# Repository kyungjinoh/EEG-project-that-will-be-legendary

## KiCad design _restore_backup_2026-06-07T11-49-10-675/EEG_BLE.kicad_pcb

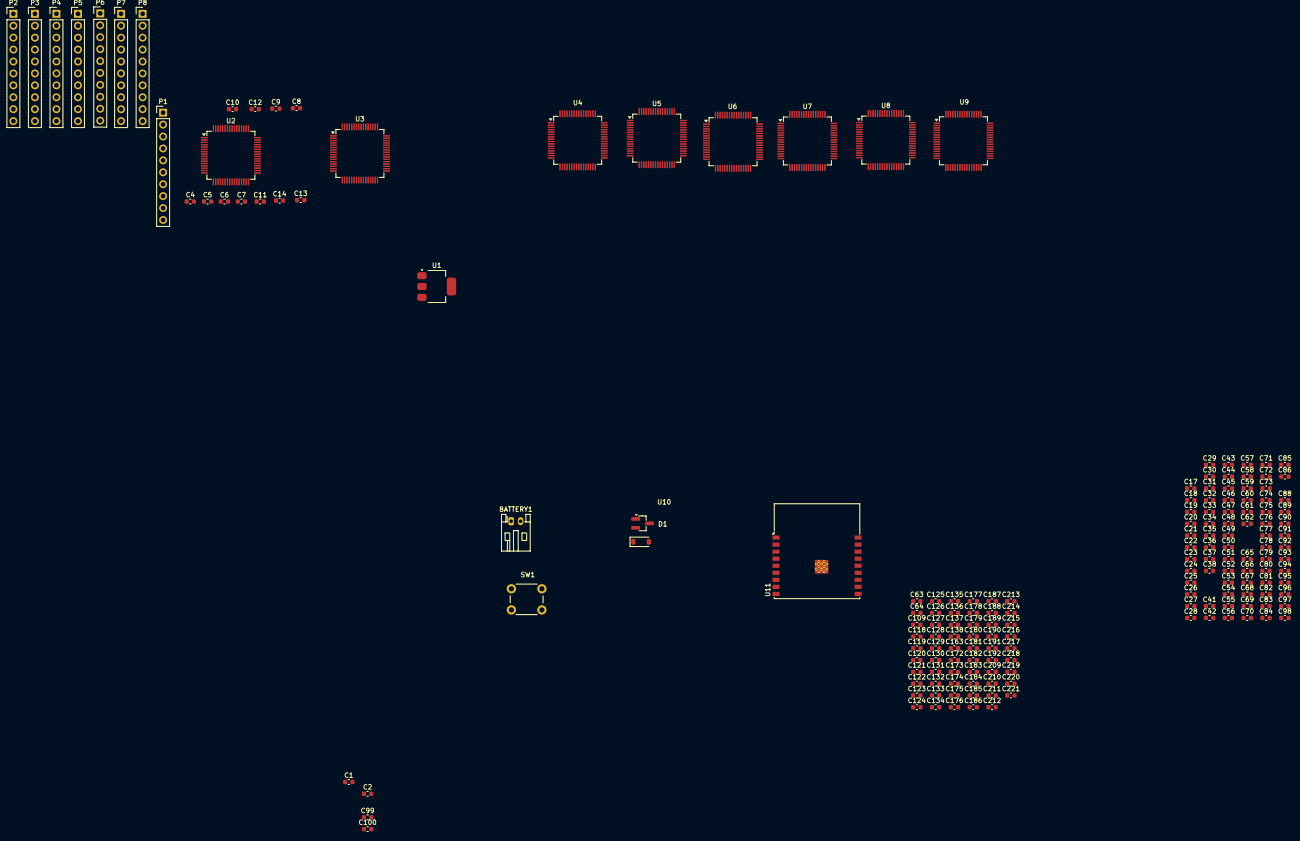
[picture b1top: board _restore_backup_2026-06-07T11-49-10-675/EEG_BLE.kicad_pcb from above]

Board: 4 copper layers, 173 parts (0 on the bottom side), 94 nets, no tracks yet.

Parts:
BATTERY1: 9V; JST_PH_S2B-PH-K_1x02_P2.00mm_Horizontal
C1: 0.33uF; C_0603_1608Metric
C2, C21, C23, C24, C28, C65, C66, C69, C70, C71, C73, C78, C81, C118, C121, C122, C124, C125, C128, C132, C135, C172, C175, C176, C178, C179, C182, C185, C190, C210, C212, C213, C217, C220, C221: 0.1uF; C_0603_1608Metric
C4, C5, C6, C7, C8, C9, C10, C11, C12, C13, C14, C17, C18, C31, C32, C33, C34, C35, C36, C37, C38, C41, C42, C43, C44, C45, C46, C47, C48, C49, C50, C51, C52, C53, C54, C55, C56, C57, C58, C59, C60, C61, C62, C85, C86, C88, C89, C90, C91, C92, C93, C94, C95, C96, C97, C98, C99, C100: 4n7; C_0603_1608Metric
C19, C63, C64, C109, C119, C163, C173, C209: 1uf; C_0603_1608Metric
C20: 1n; C_0603_1608Metric
C22, C26, C27, C30, C67, C68, C75, C76, C77, C79, C83, C84, C120, C123, C127, C130, C131, C134, C136, C138, C174, C177, C181, C184, C186, C188, C189, C192, C211, C215, C216, C219: 1uF; C_0603_1608Metric
C25, C72, C74, C126, C129, C180, C183, C214: 10uF; C_0603_1608Metric
C29, C80, C82, C133, C137, C187, C191, C218: 100uF; C_0603_1608Metric
D1: D; D_SOD-123
P1, P2, P3, P4, P5, P6, P7, P8: ELECTRODES; PinHeader_1x10_P2.54mm_Vertical
SW1: PUSH; SW_PUSH_6mm_H4.3mm
U1: LM1117MP-5.0; SOT-223-3_TabPin2
U2, U3, U4, U5, U6, U7, U8, U9: ADS1299; TQFP-64_10x10mm_P0.5mm
U10: AMS1117-3.3; SOT-23_Handsoldering
U11: ESP32-C3-WROOM-02

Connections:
/BIAS_DRV: C20.1, P1.1, P2.1, P3.1, P4.1, P5.1, P6.1, P7.1, P8.1
/BIAS_MASTER: C20.2, U2.62 (BIASIN), U2.63 (BIASOUT)
/CS: U2.39 (~CS), U3.39 (~CS), U4.39 (~CS), U5.39 (~CS), U6.39 (~CS), U7.39 (~CS), U8.39 (~CS), U9.39 (~CS), U11.7 (IO8)
/DAISY_U4: U3.41 (DAISY_IN), U4.43 (DOUT)
/DAISY_U5: U4.41 (DAISY_IN), U5.43 (DOUT)
/DAISY_U6: U5.41 (DAISY_IN), U6.43 (DOUT)
/DAISY_U7: U6.41 (DAISY_IN), U7.43 (DOUT)
/DAISY_U8: U7.41 (DAISY_IN), U8.43 (DOUT)
/DAISY_U9: U8.41 (DAISY_IN), U9.43 (DOUT)
/DRDY: U2.47 (~DRDY), U11.8 (IO9)
/EEG_REF: U2.18 (SRB2), U3.18 (SRB2), U4.18 (SRB2), U5.18 (SRB2), U6.18 (SRB2), U7.18 (SRB2), U8.18 (SRB2), U9.18 (SRB2)
/MASTER_CLK: U2.37 (CLK), U3.37 (CLK), U4.37 (CLK), U5.37 (CLK), U6.37 (CLK), U7.37 (CLK), U8.37 (CLK), U9.37 (CLK)
/REF_ELECTRODE: P1.2, P1.9, P2.2, P2.9, P3.2, P3.9, P4.2, P4.9, P5.2, P5.9, P6.2, P6.9, P7.2, P7.9, P8.2, P8.9, U2.1 (IN8N), U2.2 (IN8P), U2.3 (IN7N), U2.4 (IN7P), U2.5 (IN6N), U2.6 (IN6P), U2.7 (IN5N), U2.8 (IN5P), U2.9 (IN4N), U2.10 (IN4P), U2.11 (IN3N), U2.12 (IN3P), U2.13 (IN2N), U2.14 (IN2P), U2.15 (IN1N), U3.1 (IN8N), U3.2 (IN8P), U3.3 (IN7N), U3.4 (IN7P), U3.5 (IN6N), U3.6 (IN6P), U3.7 (IN5N), U3.8 (IN5P), U3.9 (IN4N), U3.10 (IN4P), U3.11 (IN3N), U3.12 (IN3P), U3.13 (IN2N), U3.14 (IN2P), U3.15 (IN1N), U4.1 (IN8N), U4.2 (IN8P), U4.3 (IN7N), U4.4 (IN7P), U4.5 (IN6N), U4.6 (IN6P), U4.7 (IN5N), U4.8 (IN5P), U4.9 (IN4N), U4.10 (IN4P), U4.11 (IN3N), U4.12 (IN3P), U4.13 (IN2N), U4.14 (IN2P), U4.15 (IN1N), U5.1 (IN8N), U5.2 (IN8P), U5.3 (IN7N), U5.4 (IN7P), U5.5 (IN6N), U5.6 (IN6P), U5.7 (IN5N), U5.8 (IN5P), U5.9 (IN4N), U5.10 (IN4P), U5.11 (IN3N), U5.12 (IN3P), U5.13 (IN2N), U5.14 (IN2P), U5.15 (IN1N), U6.1 (IN8N), U6.2 (IN8P), U6.3 (IN7N), U6.4 (IN7P), U6.5 (IN6N), U6.6 (IN6P), U6.7 (IN5N), U6.8 (IN5P), U6.9 (IN4N), U6.10 (IN4P), U6.11 (IN3N), U6.12 (IN3P), U6.13 (IN2N), U6.14 (IN2P), U6.15 (IN1N), U7.1 (IN8N), U7.2 (IN8P), U7.3 (IN7N), U7.4 (IN7P), U7.5 (IN6N), U7.6 (IN6P), U7.7 (IN5N), U7.8 (IN5P), U7.9 (IN4N), U7.10 (IN4P), U7.11 (IN3N), U7.12 (IN3P), U7.13 (IN2N), U7.14 (IN2P), U7.15 (IN1N), U8.1 (IN8N), U8.2 (IN8P), U8.3 (IN7N), U8.4 (IN7P), U8.5 (IN6N), U8.6 (IN6P), U8.7 (IN5N), U8.8 (IN5P), U8.9 (IN4N), U8.10 (IN4P), U8.11 (IN3N), U8.12 (IN3P), U8.13 (IN2N), U8.14 (IN2P), U8.15 (IN1N), U9.1 (IN8N), U9.2 (IN8P), U9.3 (IN7N), U9.4 (IN7P), U9.5 (IN6N), U9.6 (IN6P), U9.7 (IN5N), U9.8 (IN5P), U9.9 (IN4N), U9.10 (IN4P), U9.11 (IN3N), U9.12 (IN3P), U9.13 (IN2N), U9.14 (IN2P), U9.15 (IN1N)
/RESET: U2.36 (~RESET), U3.36 (~RESET), U4.36 (~RESET), U5.36 (~RESET), U6.36 (~RESET), U7.36 (~RESET), U8.36 (~RESET), U9.36 (~RESET), U11.3 (IO4)
/SCLK: U2.40 (SCLK), U3.40 (SCLK), U4.40 (SCLK), U5.40 (SCLK), U6.40 (SCLK), U7.40 (SCLK), U8.40 (SCLK), U9.40 (SCLK), U11.13 (IO18)
/SPI_MISO: U3.43 (DOUT), U11.4 (IO5)
/SPI_MOSI: U2.34 (DIN), U3.34 (DIN), U4.34 (DIN), U5.34 (DIN), U6.34 (DIN), U7.34 (DIN), U8.34 (DIN), U9.34 (DIN), U11.6 (IO7)
/START: U2.38 (START), U3.38 (START), U4.38 (START), U5.38 (START), U6.38 (START), U7.38 (START), U8.38 (START), U9.38 (START), U11.10 (IO10)
AGND: BATTERY1.2, C1.2, C2.1, C2.2, C220.2, C221.2, U1.1 (GND), U1.2 (VO), U2.31 (RESV1), U2.33 (DGND), U2.41 (DAISY_IN), U2.42 (GPIO1), U2.44 (GPIO2), U2.45 (GPIO3), U2.46 (GPIO4), U2.49 (DGND), U2.51 (DGND), U3.31 (RESV1), U3.33 (DGND), U3.42 (GPIO1), U3.44 (GPIO2), U3.45 (GPIO3), U3.46 (GPIO4), U3.49 (DGND), U3.51 (DGND), U3.52 (CLKSEL), U4.31 (RESV1), U4.33 (DGND), U4.42 (GPIO1), U4.44 (GPIO2), U4.45 (GPIO3), U4.46 (GPIO4), U4.49 (DGND), U4.51 (DGND), U4.52 (CLKSEL), U5.31 (RESV1), U5.33 (DGND), U5.42 (GPIO1), U5.44 (GPIO2), U5.45 (GPIO3), U5.46 (GPIO4), U5.49 (DGND), U5.51 (DGND), U5.52 (CLKSEL), U6.31 (RESV1), U6.33 (DGND), U6.42 (GPIO1), U6.44 (GPIO2), U6.45 (GPIO3), U6.46 (GPIO4), U6.49 (DGND), U6.51 (DGND), U6.52 (CLKSEL), U7.31 (RESV1), U7.33 (DGND), U7.42 (GPIO1), U7.44 (GPIO2), U7.45 (GPIO3), U7.46 (GPIO4), U7.49 (DGND), U7.51 (DGND), U7.52 (CLKSEL), U8.31 (RESV1), U8.33 (DGND), U8.42 (GPIO1), U8.44 (GPIO2), U8.45 (GPIO3), U8.46 (GPIO4), U8.49 (DGND), U8.51 (DGND), U8.52 (CLKSEL), U9.31 (RESV1), U9.33 (DGND), U9.41 (DAISY_IN), U9.42 (GPIO1), U9.44 (GPIO2), U9.45 (GPIO3), U9.46 (GPIO4), U9.49 (DGND), U9.51 (DGND), U9.52 (CLKSEL), U10.3 (GND), U11.9 (GND), U11.19 (GND)
AVDD: C19.1, C21.1, C22.1, C23.1, C63.1, C64.1, C65.1, C66.1, C67.1, C68.1, C69.1, C70.1, C109.1, C118.1, C119.1, C120.1, C121.1, C122.1, C123.1, C124.1, C163.1, C172.1, C173.1, C174.1, C175.1, C176.1, C177.1, C178.1, C209.1, C210.1, C211.1, C212.1, U2.19 (AVDD), U2.21 (AVDD), U2.22 (AVDD), U2.54 (AVDD1), U2.56 (AVDD), U2.59 (AVDD), U3.19 (AVDD), U3.21 (AVDD), U3.22 (AVDD), U3.54 (AVDD1), U3.56 (AVDD), U3.59 (AVDD), U4.19 (AVDD), U4.21 (AVDD), U4.22 (AVDD), U4.54 (AVDD1), U4.56 (AVDD), U4.59 (AVDD), U5.19 (AVDD), U5.21 (AVDD), U5.22 (AVDD), U5.54 (AVDD1), U5.56 (AVDD), U5.59 (AVDD), U6.19 (AVDD), U6.21 (AVDD), U6.22 (AVDD), U6.54 (AVDD1), U6.56 (AVDD), U6.59 (AVDD), U7.19 (AVDD), U7.21 (AVDD), U7.22 (AVDD), U7.54 (AVDD1), U7.56 (AVDD), U7.59 (AVDD), U8.19 (AVDD), U8.21 (AVDD), U8.22 (AVDD), U8.54 (AVDD1), U8.56 (AVDD), U8.59 (AVDD), U9.19 (AVDD), U9.21 (AVDD), U9.22 (AVDD), U9.54 (AVDD1), U9.56 (AVDD), U9.59 (AVDD)
AVSS: C4.1, C4.2, C8.1, C9.1, C10.1, C11.1, C12.1, C13.1, C14.1, C17.1, C18.1, C19.2, C21.2, C22.2, C23.2, C24.1, C24.2, C25.1, C25.2, C26.1, C27.2, C28.1, C29.2, C30.2, C31.1, C31.2, C32.1, C32.2, C36.1, C36.2, C37.1, C37.2, C38.1, C44.1, C45.1, C46.1, C47.1, C48.1, C49.1, C50.1, C51.1, C52.1, C53.1, C54.1, C55.1, C56.1, C57.1, C58.1, C59.1, C60.1, C61.1, C62.1, C63.2, C64.2, C65.2, C66.2, C67.2, C68.2, C69.2, C70.2, C71.1, C71.2, C72.1, C72.2, C73.1, C73.2, C74.1, C74.2, C75.1, C76.2, C77.1, C78.1, C79.2, C80.2, C81.1, C82.2, C83.2, C84.2, C85.1, C85.2, C86.1, C86.2, C90.1, C91.1, C91.2, C92.1, C92.2, C93.1, C94.1, C98.1, C99.1, C100.1, C109.2, C118.2, C119.2, C120.2, C121.2, C122.2, C123.2, C124.2, C125.1, C125.2, C126.1, C126.2, C127.1, C128.1, C128.2, C129.1, C129.2, C130.2, C131.1, C132.1, C133.2, C134.2, C135.1, C136.2, C137.2, C138.2, C163.2, C172.2, C173.2, C174.2, C175.2, C176.2, C177.2, C178.2, C179.1, C179.2, C180.1, C180.2, C181.1, C182.1, C182.2, C183.1, C183.2, C184.2, C185.1, C186.1, C187.2, C188.2, C189.2, C190.1, C191.2, C192.2, C209.2, C210.2, C211.2, C212.2, C213.1, C213.2, C214.1, C214.2, C215.1, C216.2, C217.1, C218.2, C219.2, U2.17 (SRB1), U2.20 (AVSS), U2.23 (AVSS), U2.24 (VREFP), U2.25 (VREFN), U2.32 (AVSS), U2.53 (AVSS1), U2.57 (AVSS), U2.58 (AVSS), U3.17 (SRB1), U3.20 (AVSS), U3.23 (AVSS), U3.24 (VREFP), U3.25 (VREFN), U3.32 (AVSS), U3.53 (AVSS1), U3.57 (AVSS), U3.58 (AVSS), U4.17 (SRB1), U4.20 (AVSS), U4.23 (AVSS), U4.24 (VREFP), U4.25 (VREFN), U4.32 (AVSS), U4.53 (AVSS1), U4.57 (AVSS), U4.58 (AVSS), U5.17 (SRB1), U5.20 (AVSS), U5.23 (AVSS), U5.24 (VREFP), U5.25 (VREFN), U5.32 (AVSS), U5.53 (AVSS1), U5.57 (AVSS), U5.58 (AVSS), U6.17 (SRB1), U6.20 (AVSS), U6.23 (AVSS), U6.24 (VREFP), U6.25 (VREFN), U6.32 (AVSS), U6.53 (AVSS1), U6.57 (AVSS), U6.58 (AVSS), U7.17 (SRB1), U7.20 (AVSS), U7.23 (AVSS), U7.24 (VREFP), U7.25 (VREFN), U7.32 (AVSS), U7.53 (AVSS1), U7.57 (AVSS), U7.58 (AVSS), U8.17 (SRB1), U8.20 (AVSS), U8.23 (AVSS), U8.24 (VREFP), U8.25 (VREFN), U8.32 (AVSS), U8.53 (AVSS1), U8.57 (AVSS), U8.58 (AVSS), U9.17 (SRB1), U9.20 (AVSS), U9.23 (AVSS), U9.24 (VREFP), U9.25 (VREFN), U9.32 (AVSS), U9.53 (AVSS1), U9.57 (AVSS), U9.58 (AVSS)
DVDD: C221.1, U2.35 (~PWDN), U2.48 (DVDD), U2.50 (DVDD), U2.52 (CLKSEL), U3.35 (~PWDN), U3.48 (DVDD), U3.50 (DVDD), U4.35 (~PWDN), U4.48 (DVDD), U4.50 (DVDD), U5.35 (~PWDN), U5.48 (DVDD), U5.50 (DVDD), U6.35 (~PWDN), U6.48 (DVDD), U6.50 (DVDD), U7.35 (~PWDN), U7.48 (DVDD), U7.50 (DVDD), U8.35 (~PWDN), U8.48 (DVDD), U8.50 (DVDD), U9.35 (~PWDN), U9.48 (DVDD), U9.50 (DVDD), U10.1 (VOUT), U11.1 (3V3), U11.2 (EN)
unnamed: BATTERY1.1, SW1.1
unnamed: D1.2 (A), SW1.2
unnamed: C6.1, C9.2, P1.3
unnamed: C7.1, C10.2, P1.4
unnamed: C5.1, C8.2, P1.5
unnamed: C6.2, P1.6
unnamed: C7.2, P1.7
unnamed: C5.2, P1.8
unnamed: P1.10, U2.16 (IN1P)
unnamed: C34.1, P2.3
unnamed: C35.1, P2.4
unnamed: C33.1, C38.2, P2.5
unnamed: C34.2, P2.6
unnamed: C35.2, P2.7
unnamed: C33.2, P2.8
unnamed: P2.10, U3.16 (IN1P)
unnamed: C42.1, C45.2, P3.3
unnamed: C43.1, C46.2, P3.4
unnamed: C41.1, C44.2, P3.5
unnamed: C42.2, P3.6
unnamed: C43.2, P3.7
unnamed: C41.2, P3.8
unnamed: P3.10, U4.16 (IN1P)
unnamed: C88.1, C93.2, P4.3
unnamed: C89.1, C94.2, P4.4
unnamed: C90.2, P4.5
unnamed: C88.2, P4.6
unnamed: C89.2, P4.7
unnamed: P4.10, U5.16 (IN1P)
unnamed: C96.1, C99.2, P5.3
unnamed: C97.1, C100.2, P5.4
unnamed: C95.1, C98.2, P5.5
unnamed: C96.2, P5.6
unnamed: C97.2, P5.7
unnamed: C95.2, P5.8
unnamed: P5.10, U6.16 (IN1P)
unnamed: P6.10, U7.16 (IN1P)
unnamed: P7.10, U8.16 (IN1P)
unnamed: P8.10, U9.16 (IN1P)
unnamed: C29.1, U2.28 (VCAP1)
unnamed: C30.1, U2.30 (VCAP2)
unnamed: C26.2, C28.2, U2.55 (VCAP3)
unnamed: C27.1, U2.26 (VCAP4)
unnamed: C80.1, U3.28 (VCAP1)
unnamed: C83.1, U3.30 (VCAP2)
unnamed: C75.2, C78.2, U3.55 (VCAP3)
unnamed: C76.1, U3.26 (VCAP4)
unnamed: C82.1, U4.28 (VCAP1)
unnamed: C84.1, U4.30 (VCAP2)
unnamed: C77.2, C81.2, U4.55 (VCAP3)
unnamed: C79.1, U4.26 (VCAP4)
unnamed: C133.1, U5.28 (VCAP1)
unnamed: C136.1, U5.30 (VCAP2)
unnamed: C127.2, C132.2, U5.55 (VCAP3)
unnamed: C130.1, U5.26 (VCAP4)
unnamed: C137.1, U6.28 (VCAP1)
unnamed: C138.1, U6.30 (VCAP2)
unnamed: C131.2, C135.2, U6.55 (VCAP3)
unnamed: C134.1, U6.26 (VCAP4)
unnamed: C187.1, U7.28 (VCAP1)
unnamed: C189.1, U7.30 (VCAP2)
unnamed: C181.2, C185.2, U7.55 (VCAP3)
unnamed: C184.1, U7.26 (VCAP4)
unnamed: C191.1, U8.28 (VCAP1)
unnamed: C192.1, U8.30 (VCAP2)
unnamed: C186.2, C190.2, U8.55 (VCAP3)
unnamed: C188.1, U8.26 (VCAP4)
unnamed: C218.1, U9.28 (VCAP1)
unnamed: C219.1, U9.30 (VCAP2)
unnamed: C215.2, C217.2, U9.55 (VCAP3)
unnamed: C216.1, U9.26 (VCAP4)
RAW: C1.1, C220.1, D1.1 (K), U1.3 (VI), U10.2 (VIN)

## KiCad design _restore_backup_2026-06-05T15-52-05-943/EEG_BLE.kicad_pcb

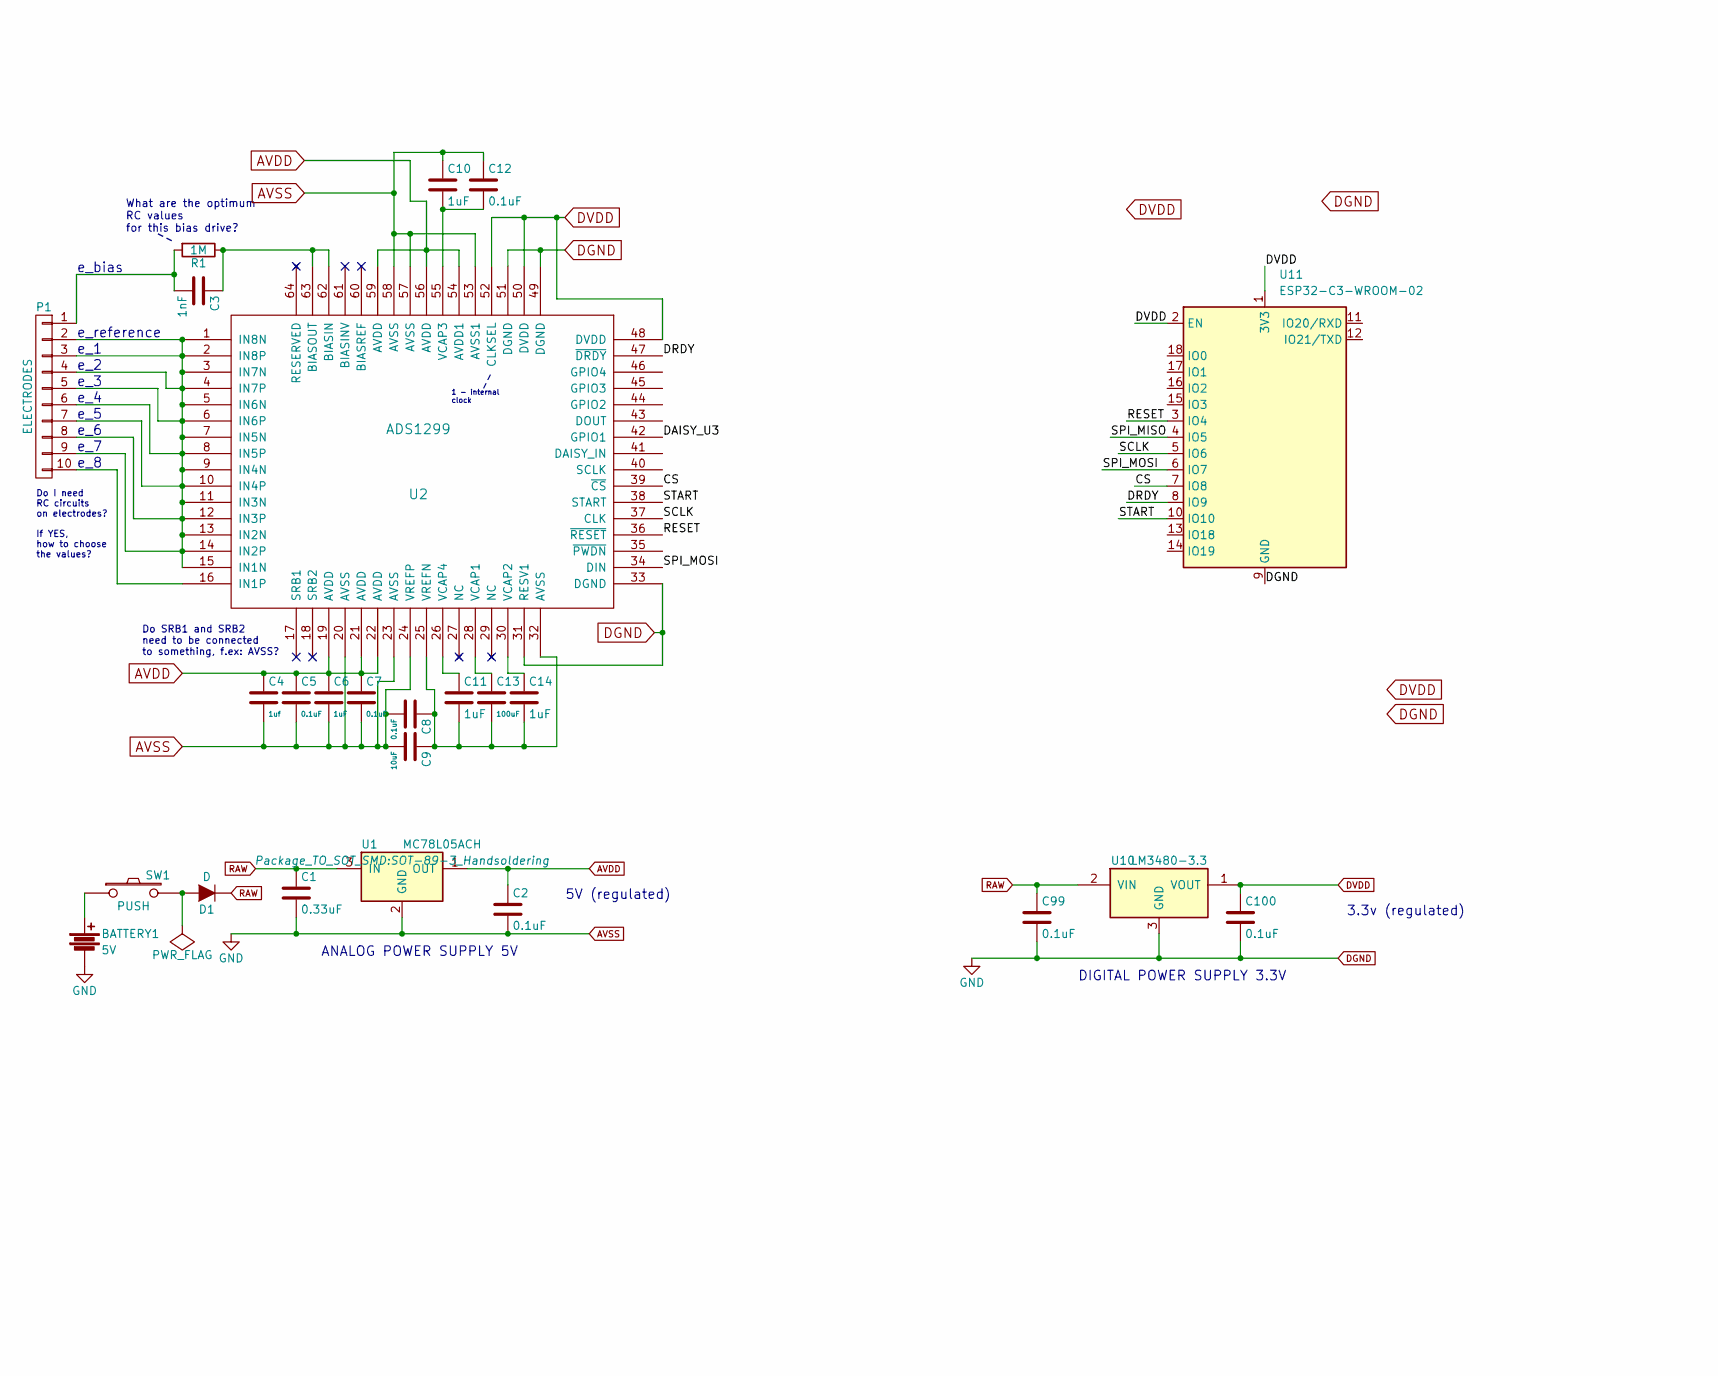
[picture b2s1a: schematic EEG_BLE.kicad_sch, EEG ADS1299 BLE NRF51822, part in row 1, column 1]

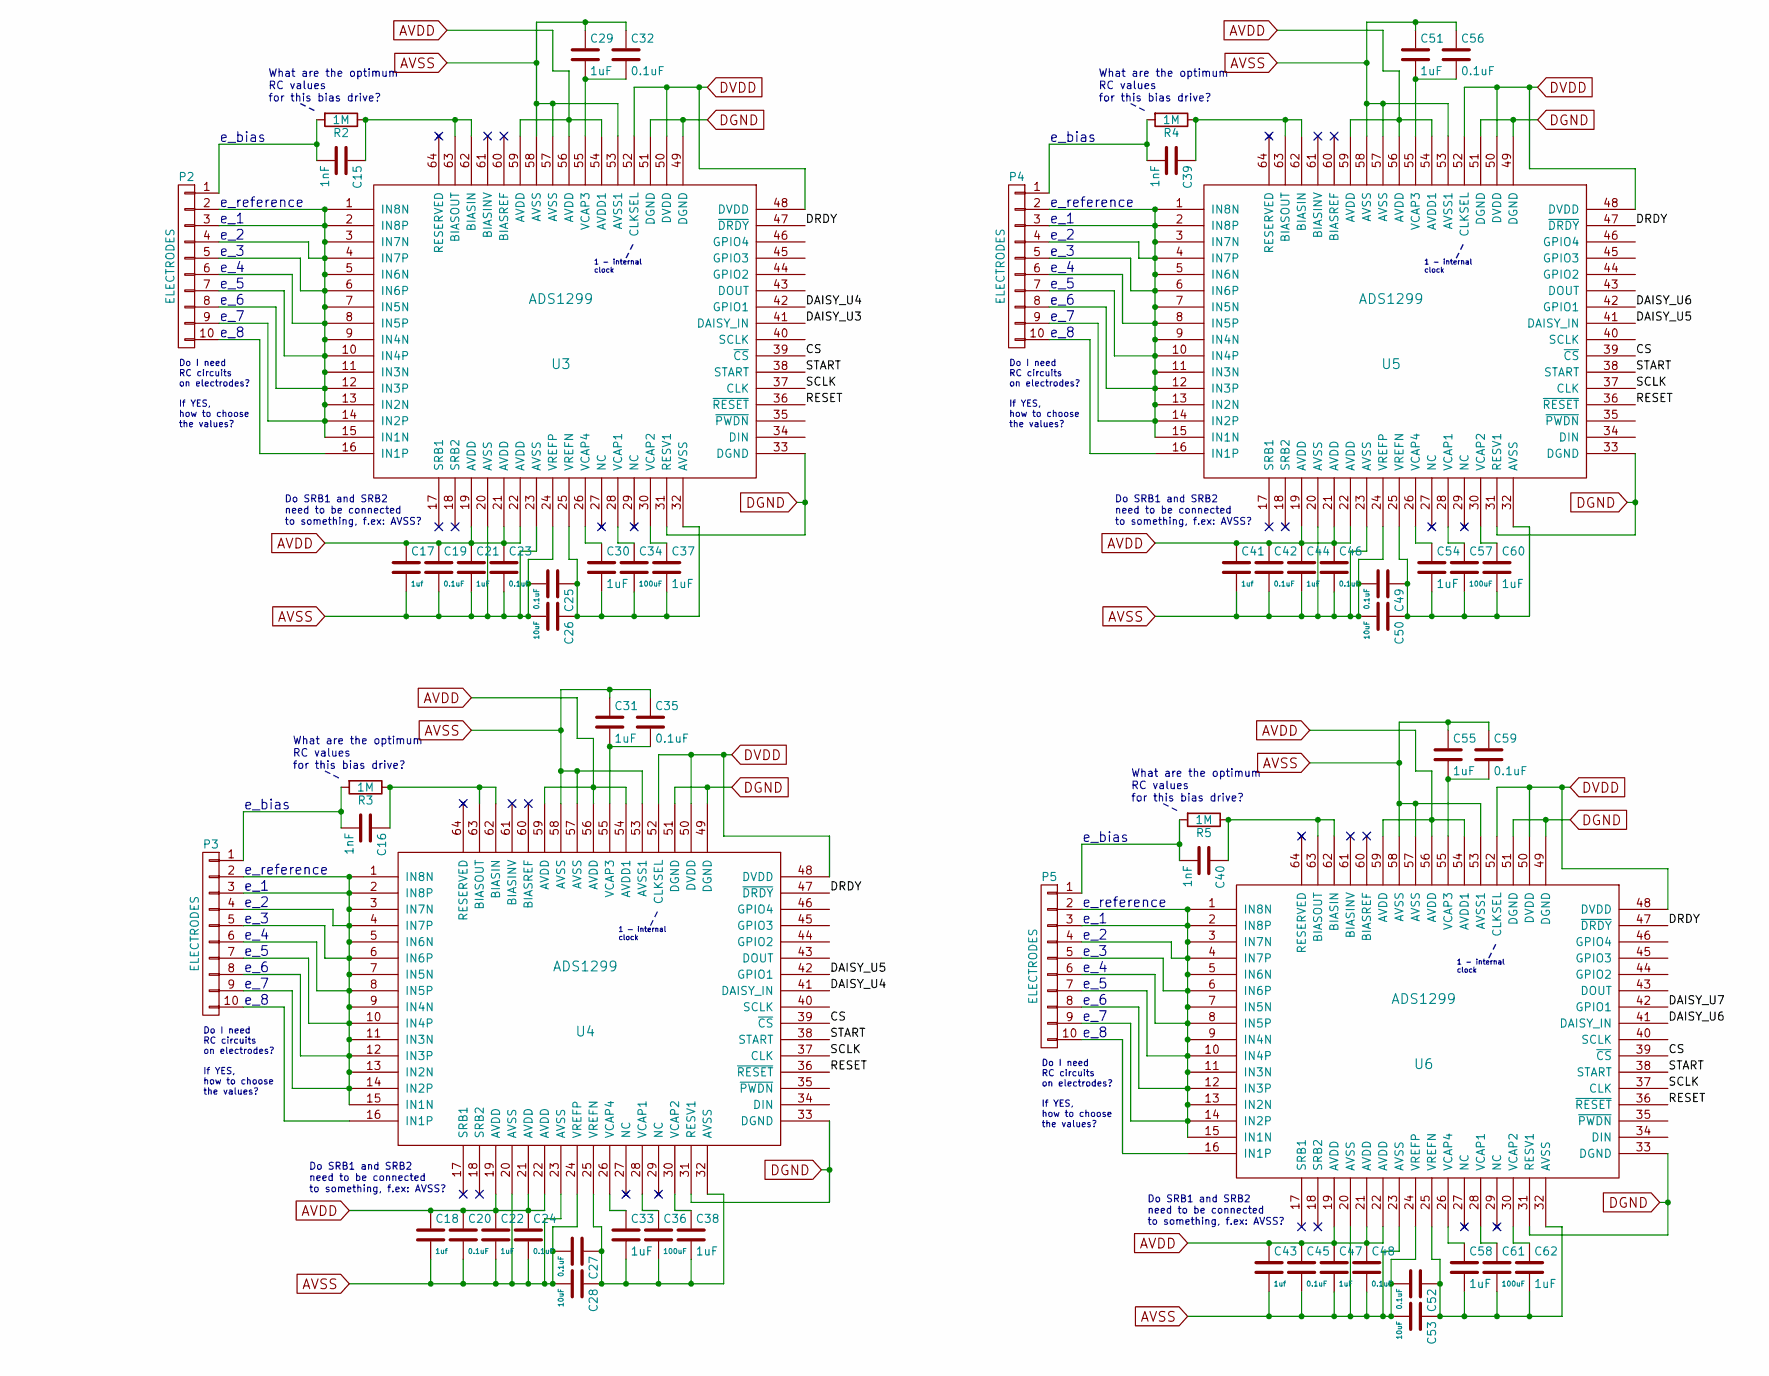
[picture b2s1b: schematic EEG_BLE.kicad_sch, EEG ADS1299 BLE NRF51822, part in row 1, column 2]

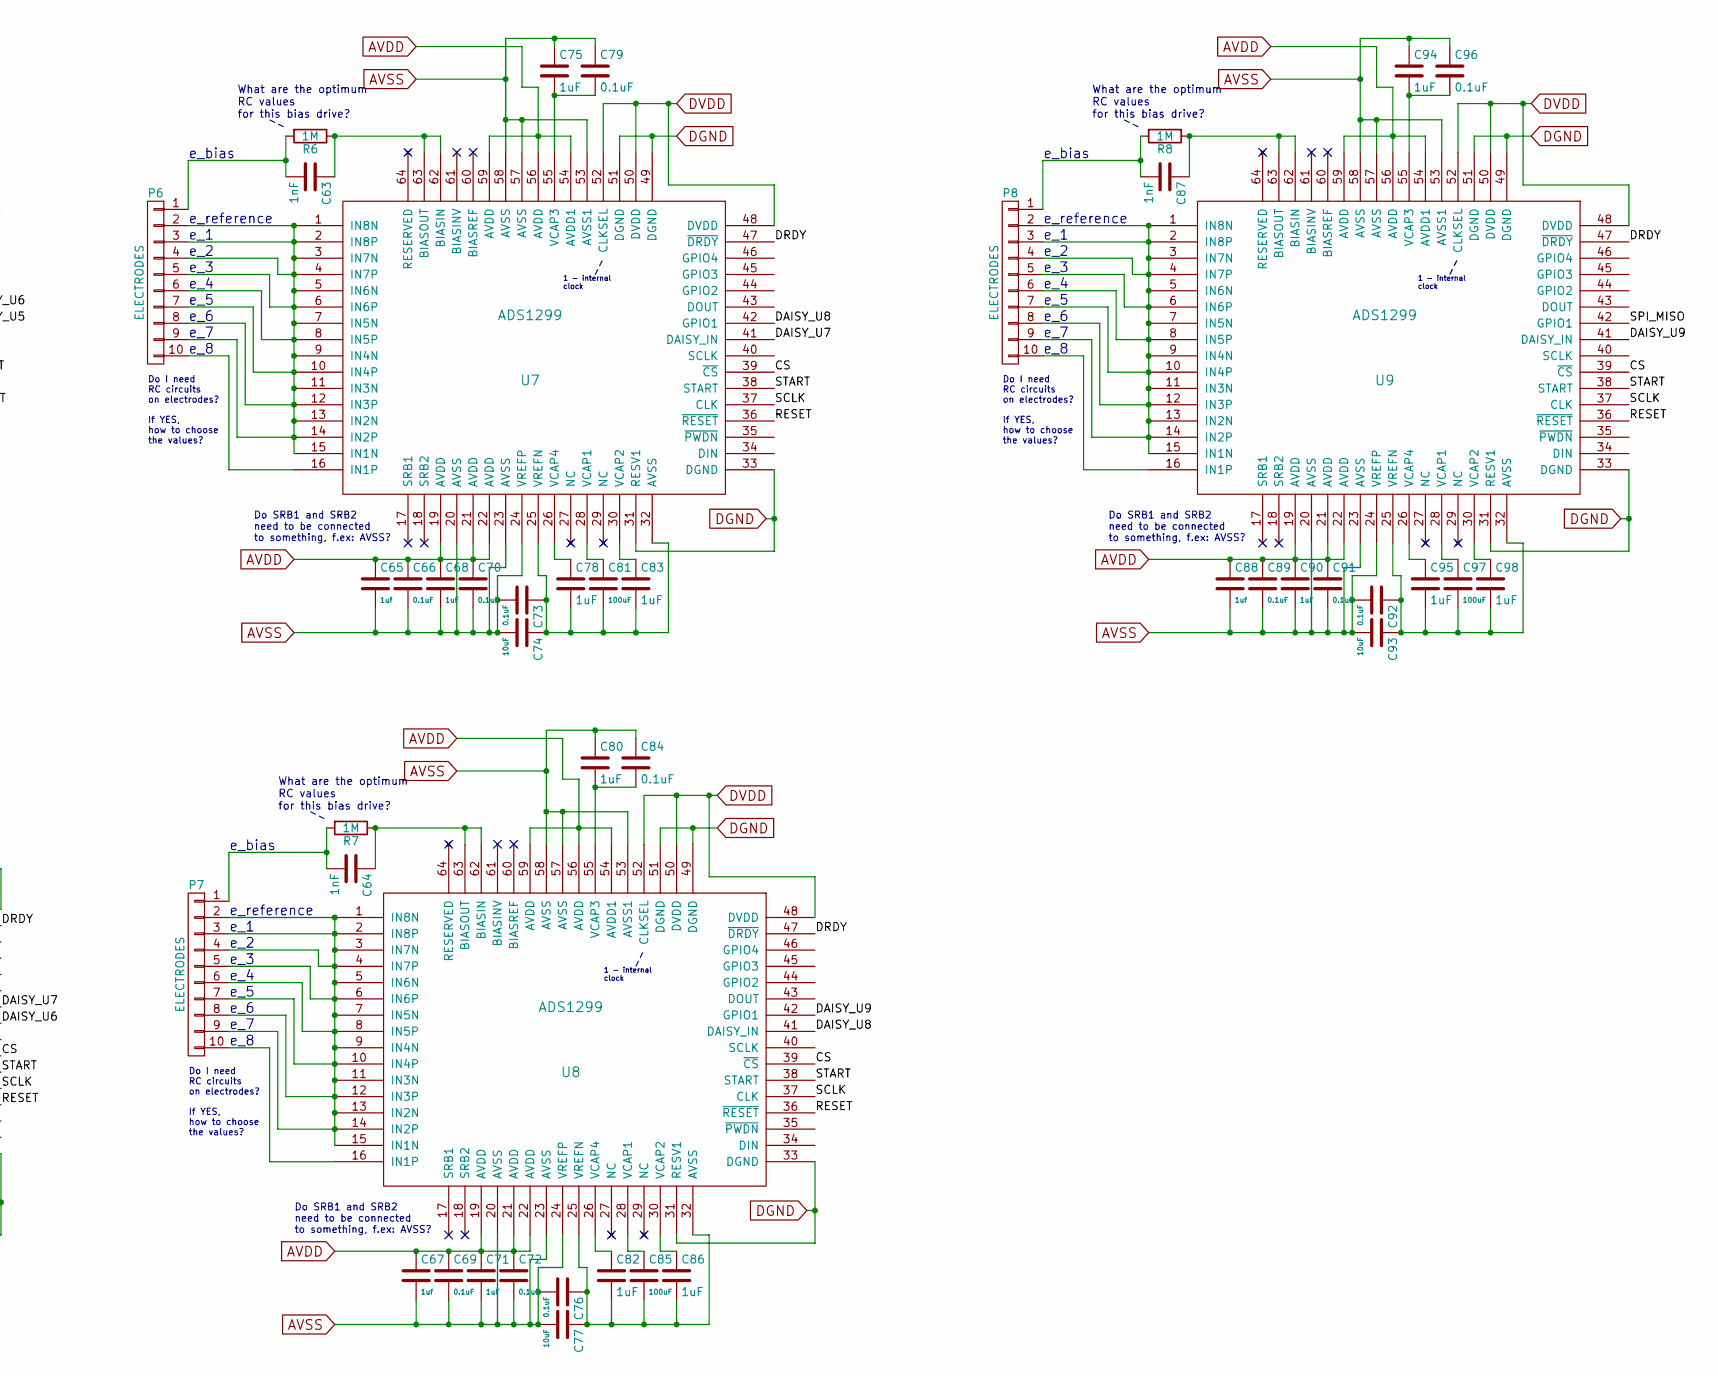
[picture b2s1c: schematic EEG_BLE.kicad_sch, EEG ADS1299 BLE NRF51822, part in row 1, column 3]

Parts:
BATTERY1: 5V; JST_PH_S2B-PH-K_1x02_P2.00mm_Horizontal
C1: 0.33uF; C_0603_1608Metric
C2, C5, C7, C8, C12, C19, C20, C23, C24, C25, C27, C32, C35, C42, C45, C46, C48, C49, C52, C56, C59, C66, C69, C70, C72, C73, C76, C79, C84, C89, C91, C92, C96, C99, C100: 0.1uF; C_0603_1608Metric
C3, C15, C16, C39, C40, C63, C64, C87: 1nF; C_0603_1608Metric
C4, C17, C18, C41, C43, C65, C67, C88: 1uf; C_0603_1608Metric
C6, C10, C11, C14, C21, C22, C29, C30, C31, C33, C37, C38, C44, C47, C51, C54, C55, C58, C60, C62, C68, C71, C75, C78, C80, C82, C83, C86, C90, C94, C95, C98: 1uF; C_0603_1608Metric
C9, C26, C28, C50, C53, C74, C77, C93: 10uF; C_0603_1608Metric
C13, C34, C36, C57, C61, C81, C85, C97: 100uF; C_0603_1608Metric
D1: D; D_SOD-123
P1, P2, P3, P4, P5, P6, P7, P8: ELECTRODES; PinHeader_1x10_P2.54mm_Vertical
R1, R2, R3, R4, R5, R6, R7, R8: 1M; R_0603_1608Metric
SW1: PUSH; SW_PUSH_6mm_H4.3mm
U1: MC78L05ACH; SOT-89-3_Handsoldering
U2, U3, U4, U5, U6, U7, U8, U9: ADS1299; TQFP-64_10x10mm_P0.5mm
U10: LM3480-3.3; SOT-23_Handsoldering
U11: ESP32-C3-WROOM-02

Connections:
/CS: U2.39 (~CS), U3.39 (~CS), U4.39 (~CS), U5.39 (~CS), U6.39 (~CS), U7.39 (~CS), U8.39 (~CS), U9.39 (~CS), U11.7 (IO8)
/DAISY_U3: U2.42 (GPIO1), U3.41 (DAISY_IN)
/DAISY_U4: U3.42 (GPIO1), U4.41 (DAISY_IN)
/DAISY_U5: U4.42 (GPIO1), U5.41 (DAISY_IN)
/DAISY_U6: U5.42 (GPIO1), U6.41 (DAISY_IN)
/DAISY_U7: U6.42 (GPIO1), U7.41 (DAISY_IN)
/DAISY_U8: U7.42 (GPIO1), U8.41 (DAISY_IN)
/DAISY_U9: U8.42 (GPIO1), U9.41 (DAISY_IN)
/DRDY: U2.47 (~DRDY), U3.47 (~DRDY), U4.47 (~DRDY), U5.47 (~DRDY), U6.47 (~DRDY), U7.47 (~DRDY), U8.47 (~DRDY), U9.47 (~DRDY), U11.8 (IO9)
/RESET: U2.36 (~RESET), U3.36 (~RESET), U4.36 (~RESET), U5.36 (~RESET), U6.36 (~RESET), U7.36 (~RESET), U8.36 (~RESET), U9.36 (~RESET), U11.3 (IO4)
/SCLK: U2.37 (CLK), U3.37 (CLK), U4.37 (CLK), U5.37 (CLK), U6.37 (CLK), U7.37 (CLK), U8.37 (CLK), U9.37 (CLK), U11.5 (IO6)
/SPI_MISO: U9.42 (GPIO1), U11.4 (IO5)
/SPI_MOSI: U2.34 (DIN), U11.6 (IO7)
/START: U2.38 (START), U3.38 (START), U4.38 (START), U5.38 (START), U6.38 (START), U7.38 (START), U8.38 (START), U9.38 (START), U11.10 (IO10)
AVDD: C2.1, C4.1, C5.1, C6.1, C7.1, C17.1, C18.1, C19.1, C20.1, C21.1, C22.1, C23.1, C24.1, C41.1, C42.1, C43.1, C44.1, C45.1, C46.1, C47.1, C48.1, C65.1, C66.1, C67.1, C68.1, C69.1, C70.1, C71.1, C72.1, C88.1, C89.1, C90.1, C91.1, U1.1 (OUT), U2.19 (AVDD), U2.21 (AVDD), U2.22 (AVDD), U2.54 (AVDD1), U2.56 (AVDD), U2.59 (AVDD), U3.19 (AVDD), U3.21 (AVDD), U3.22 (AVDD), U3.54 (AVDD1), U3.56 (AVDD), U3.59 (AVDD), U4.19 (AVDD), U4.21 (AVDD), U4.22 (AVDD), U4.54 (AVDD1), U4.56 (AVDD), U4.59 (AVDD), U5.19 (AVDD), U5.21 (AVDD), U5.22 (AVDD), U5.54 (AVDD1), U5.56 (AVDD), U5.59 (AVDD), U6.19 (AVDD), U6.21 (AVDD), U6.22 (AVDD), U6.54 (AVDD1), U6.56 (AVDD), U6.59 (AVDD), U7.19 (AVDD), U7.21 (AVDD), U7.22 (AVDD), U7.54 (AVDD1), U7.56 (AVDD), U7.59 (AVDD), U8.19 (AVDD), U8.21 (AVDD), U8.22 (AVDD), U8.54 (AVDD1), U8.56 (AVDD), U8.59 (AVDD), U9.19 (AVDD), U9.21 (AVDD), U9.22 (AVDD), U9.54 (AVDD1), U9.56 (AVDD), U9.59 (AVDD)
AVSS: BATTERY1.2, C1.2, C2.2, C4.2, C5.2, C6.2, C7.2, C8.2, C9.2, C10.1, C12.1, C17.2, C18.2, C19.2, C20.2, C21.2, C22.2, C23.2, C24.2, C25.2, C26.2, C27.2, C28.2, C29.1, C31.1, C32.1, C35.1, C41.2, C42.2, C43.2, C44.2, C45.2, C46.2, C47.2, C48.2, C49.2, C50.2, C51.1, C52.2, C53.2, C55.1, C56.1, C59.1, C65.2, C66.2, C67.2, C68.2, C69.2, C70.2, C71.2, C72.2, C73.2, C74.2, C75.1, C76.2, C77.2, C79.1, C80.1, C84.1, C88.2, C89.2, C90.2, C91.2, C92.2, C93.2, C94.1, C96.1, C99.2, C100.2, U1.2 (GND), U2.20 (AVSS), U2.23 (AVSS), U2.24 (VREFP), U2.31 (RESV1), U2.33 (DGND), U2.49 (DGND), U2.51 (DGND), U2.53 (AVSS1), U2.57 (AVSS), U2.58 (AVSS), U3.20 (AVSS), U3.23 (AVSS), U3.24 (VREFP), U3.31 (RESV1), U3.33 (DGND), U3.49 (DGND), U3.51 (DGND), U3.53 (AVSS1), U3.57 (AVSS), U3.58 (AVSS), U4.20 (AVSS), U4.23 (AVSS), U4.24 (VREFP), U4.31 (RESV1), U4.33 (DGND), U4.49 (DGND), U4.51 (DGND), U4.53 (AVSS1), U4.57 (AVSS), U4.58 (AVSS), U5.20 (AVSS), U5.23 (AVSS), U5.24 (VREFP), U5.31 (RESV1), U5.33 (DGND), U5.49 (DGND), U5.51 (DGND), U5.53 (AVSS1), U5.57 (AVSS), U5.58 (AVSS), U6.20 (AVSS), U6.23 (AVSS), U6.24 (VREFP), U6.31 (RESV1), U6.33 (DGND), U6.49 (DGND), U6.51 (DGND), U6.53 (AVSS1), U6.57 (AVSS), U6.58 (AVSS), U7.20 (AVSS), U7.23 (AVSS), U7.24 (VREFP), U7.31 (RESV1), U7.33 (DGND), U7.49 (DGND), U7.51 (DGND), U7.53 (AVSS1), U7.57 (AVSS), U7.58 (AVSS), U8.20 (AVSS), U8.23 (AVSS), U8.24 (VREFP), U8.31 (RESV1), U8.33 (DGND), U8.49 (DGND), U8.51 (DGND), U8.53 (AVSS1), U8.57 (AVSS), U8.58 (AVSS), U9.20 (AVSS), U9.23 (AVSS), U9.24 (VREFP), U9.31 (RESV1), U9.33 (DGND), U9.49 (DGND), U9.51 (DGND), U9.53 (AVSS1), U9.57 (AVSS), U9.58 (AVSS), U10.3 (GND), U11.9 (GND), U11.19 (GND)
DVDD: C100.1, U2.48 (DVDD), U2.50 (DVDD), U2.52 (CLKSEL), U3.48 (DVDD), U3.50 (DVDD), U3.52 (CLKSEL), U4.48 (DVDD), U4.50 (DVDD), U4.52 (CLKSEL), U5.48 (DVDD), U5.50 (DVDD), U5.52 (CLKSEL), U6.48 (DVDD), U6.50 (DVDD), U6.52 (CLKSEL), U7.48 (DVDD), U7.50 (DVDD), U7.52 (CLKSEL), U8.48 (DVDD), U8.50 (DVDD), U8.52 (CLKSEL), U9.48 (DVDD), U9.50 (DVDD), U9.52 (CLKSEL), U10.1 (VOUT), U11.1 (3V3), U11.2 (EN)
unnamed: BATTERY1.1, SW1.1
unnamed: D1.2 (A), SW1.2
unnamed: C3.2, P1.1, R1.2
unnamed: P1.2, P1.3, P1.4, P1.5, P1.6, P1.7, P1.8, P1.9, U2.1 (IN8N), U2.2 (IN8P), U2.3 (IN7N), U2.4 (IN7P), U2.5 (IN6N), U2.6 (IN6P), U2.7 (IN5N), U2.8 (IN5P), U2.9 (IN4N), U2.10 (IN4P), U2.11 (IN3N), U2.12 (IN3P), U2.13 (IN2N), U2.14 (IN2P), U2.15 (IN1N)
unnamed: P1.10, U2.16 (IN1P)
unnamed: C15.2, P2.1, R2.2
unnamed: P2.2, P2.3, P2.4, P2.5, P2.6, P2.7, P2.8, P2.9, U3.1 (IN8N), U3.2 (IN8P), U3.3 (IN7N), U3.4 (IN7P), U3.5 (IN6N), U3.6 (IN6P), U3.7 (IN5N), U3.8 (IN5P), U3.9 (IN4N), U3.10 (IN4P), U3.11 (IN3N), U3.12 (IN3P), U3.13 (IN2N), U3.14 (IN2P), U3.15 (IN1N)
unnamed: P2.10, U3.16 (IN1P)
unnamed: C16.2, P3.1, R3.2
unnamed: P3.2, P3.3, P3.4, P3.5, P3.6, P3.7, P3.8, P3.9, U4.1 (IN8N), U4.2 (IN8P), U4.3 (IN7N), U4.4 (IN7P), U4.5 (IN6N), U4.6 (IN6P), U4.7 (IN5N), U4.8 (IN5P), U4.9 (IN4N), U4.10 (IN4P), U4.11 (IN3N), U4.12 (IN3P), U4.13 (IN2N), U4.14 (IN2P), U4.15 (IN1N)
unnamed: P3.10, U4.16 (IN1P)
unnamed: C39.2, P4.1, R4.2
unnamed: P4.2, P4.3, P4.4, P4.5, P4.6, P4.7, P4.8, P4.9, U5.1 (IN8N), U5.2 (IN8P), U5.3 (IN7N), U5.4 (IN7P), U5.5 (IN6N), U5.6 (IN6P), U5.7 (IN5N), U5.8 (IN5P), U5.9 (IN4N), U5.10 (IN4P), U5.11 (IN3N), U5.12 (IN3P), U5.13 (IN2N), U5.14 (IN2P), U5.15 (IN1N)
unnamed: P4.10, U5.16 (IN1P)
unnamed: C40.2, P5.1, R5.2
unnamed: P5.2, P5.3, P5.4, P5.5, P5.6, P5.7, P5.8, P5.9, U6.1 (IN8N), U6.2 (IN8P), U6.3 (IN7N), U6.4 (IN7P), U6.5 (IN6N), U6.6 (IN6P), U6.7 (IN5N), U6.8 (IN5P), U6.9 (IN4N), U6.10 (IN4P), U6.11 (IN3N), U6.12 (IN3P), U6.13 (IN2N), U6.14 (IN2P), U6.15 (IN1N)
unnamed: P5.10, U6.16 (IN1P)
unnamed: C63.2, P6.1, R6.2
unnamed: P6.2, P6.3, P6.4, P6.5, P6.6, P6.7, P6.8, P6.9, U7.1 (IN8N), U7.2 (IN8P), U7.3 (IN7N), U7.4 (IN7P), U7.5 (IN6N), U7.6 (IN6P), U7.7 (IN5N), U7.8 (IN5P), U7.9 (IN4N), U7.10 (IN4P), U7.11 (IN3N), U7.12 (IN3P), U7.13 (IN2N), U7.14 (IN2P), U7.15 (IN1N)
unnamed: P6.10, U7.16 (IN1P)
unnamed: C64.2, P7.1, R7.2
unnamed: P7.2, P7.3, P7.4, P7.5, P7.6, P7.7, P7.8, P7.9, U8.1 (IN8N), U8.2 (IN8P), U8.3 (IN7N), U8.4 (IN7P), U8.5 (IN6N), U8.6 (IN6P), U8.7 (IN5N), U8.8 (IN5P), U8.9 (IN4N), U8.10 (IN4P), U8.11 (IN3N), U8.12 (IN3P), U8.13 (IN2N), U8.14 (IN2P), U8.15 (IN1N)
unnamed: P7.10, U8.16 (IN1P)
unnamed: C87.2, P8.1, R8.2
unnamed: P8.2, P8.3, P8.4, P8.5, P8.6, P8.7, P8.8, P8.9, U9.1 (IN8N), U9.2 (IN8P), U9.3 (IN7N), U9.4 (IN7P), U9.5 (IN6N), U9.6 (IN6P), U9.7 (IN5N), U9.8 (IN5P), U9.9 (IN4N), U9.10 (IN4P), U9.11 (IN3N), U9.12 (IN3P), U9.13 (IN2N), U9.14 (IN2P), U9.15 (IN1N)
unnamed: P8.10, U9.16 (IN1P)
unnamed: C3.1, R1.1, U2.62 (BIASIN), U2.63 (BIASOUT)
unnamed: C13.1, U2.28 (VCAP1)
unnamed: C14.1, U2.30 (VCAP2)
unnamed: C10.2, C12.2, U2.55 (VCAP3)
unnamed: C11.1, U2.26 (VCAP4)
unnamed: C8.1, C9.1, C11.2, C13.2, C14.2, U2.25 (VREFN), U2.32 (AVSS)
unnamed: C15.1, R2.1, U3.62 (BIASIN), U3.63 (BIASOUT)
unnamed: C34.1, U3.28 (VCAP1)
unnamed: C37.1, U3.30 (VCAP2)
unnamed: C29.2, C32.2, U3.55 (VCAP3)
unnamed: C30.1, U3.26 (VCAP4)
unnamed: C25.1, C26.1, C30.2, C34.2, C37.2, U3.25 (VREFN), U3.32 (AVSS)
unnamed: C16.1, R3.1, U4.62 (BIASIN), U4.63 (BIASOUT)
unnamed: C36.1, U4.28 (VCAP1)
unnamed: C38.1, U4.30 (VCAP2)
unnamed: C31.2, C35.2, U4.55 (VCAP3)
unnamed: C33.1, U4.26 (VCAP4)
unnamed: C27.1, C28.1, C33.2, C36.2, C38.2, U4.25 (VREFN), U4.32 (AVSS)
unnamed: C39.1, R4.1, U5.62 (BIASIN), U5.63 (BIASOUT)
unnamed: C57.1, U5.28 (VCAP1)
unnamed: C60.1, U5.30 (VCAP2)
unnamed: C51.2, C56.2, U5.55 (VCAP3)
unnamed: C54.1, U5.26 (VCAP4)
unnamed: C49.1, C50.1, C54.2, C57.2, C60.2, U5.25 (VREFN), U5.32 (AVSS)
unnamed: C40.1, R5.1, U6.62 (BIASIN), U6.63 (BIASOUT)
unnamed: C61.1, U6.28 (VCAP1)
unnamed: C62.1, U6.30 (VCAP2)
unnamed: C55.2, C59.2, U6.55 (VCAP3)
unnamed: C58.1, U6.26 (VCAP4)
unnamed: C52.1, C53.1, C58.2, C61.2, C62.2, U6.25 (VREFN), U6.32 (AVSS)
unnamed: C63.1, R6.1, U7.62 (BIASIN), U7.63 (BIASOUT)
unnamed: C81.1, U7.28 (VCAP1)
unnamed: C83.1, U7.30 (VCAP2)
unnamed: C75.2, C79.2, U7.55 (VCAP3)
unnamed: C78.1, U7.26 (VCAP4)
unnamed: C73.1, C74.1, C78.2, C81.2, C83.2, U7.25 (VREFN), U7.32 (AVSS)
unnamed: C64.1, R7.1, U8.62 (BIASIN), U8.63 (BIASOUT)
unnamed: C85.1, U8.28 (VCAP1)
unnamed: C86.1, U8.30 (VCAP2)
unnamed: C80.2, C84.2, U8.55 (VCAP3)
unnamed: C82.1, U8.26 (VCAP4)
unnamed: C76.1, C77.1, C82.2, C85.2, C86.2, U8.25 (VREFN), U8.32 (AVSS)
unnamed: C87.1, R8.1, U9.62 (BIASIN), U9.63 (BIASOUT)
unnamed: C97.1, U9.28 (VCAP1)
unnamed: C98.1, U9.30 (VCAP2)
unnamed: C94.2, C96.2, U9.55 (VCAP3)
unnamed: C95.1, U9.26 (VCAP4)
unnamed: C92.1, C93.1, C95.2, C97.2, C98.2, U9.25 (VREFN), U9.32 (AVSS)
RAW: C1.1, C99.1, D1.1 (K), U1.3 (IN), U10.2 (VIN)

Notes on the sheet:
What are the optimum RC values for this bias drive?
e_7
1 - internal clock
e_8
e_bias
Do SRB1 and SRB2 need to be connected to something, f.ex: AVSS?
Do I need RC circuits on electrodes?
e_2
e_1
If YES, how to choose the values?
e_6
e_4
e_3
e_reference
ANALOG POWER SUPPLY 5V
5V (regulated)
DIGITAL POWER SUPPLY 3.3V
e_5
3.3v (regulated)

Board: 4 copper layers, 130 parts (0 on the bottom side), 92 nets, no tracks yet.
